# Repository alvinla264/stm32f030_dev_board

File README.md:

# STM32F030 Dev Board

This is a custom development board for the STM32F030RCT6 with USB-C and FT232H for USB-to-serial communication and SWD ports for debugging. Designed as a 4-layer board.

---

## 📷 Schematic

---

## 🖼️ PCB Layout

### 2D Layout:

### 3D Preview:

---

## 🔧 Stackup

- Layer 1 (Top): Signal + GND pours
- Layer 2: GND
- Layer 3: Power (3.3V plane)
- Layer 4 (Bottom): Signal + GND pours

---

## 📌 Features

- STM32F030RCT6 (64-pin LQFP)
- USB-C for power and data
- FT232H for USB-to-UART
- SWD ports for debugging
- Decoupling and filtering capacitors throughout

---

## 💡 Status

- ✔️ Schematic complete
- ✔️ PCB layout complete
- ❌ Via Stitching in progress
- ❌ Testing and fabrication in progress

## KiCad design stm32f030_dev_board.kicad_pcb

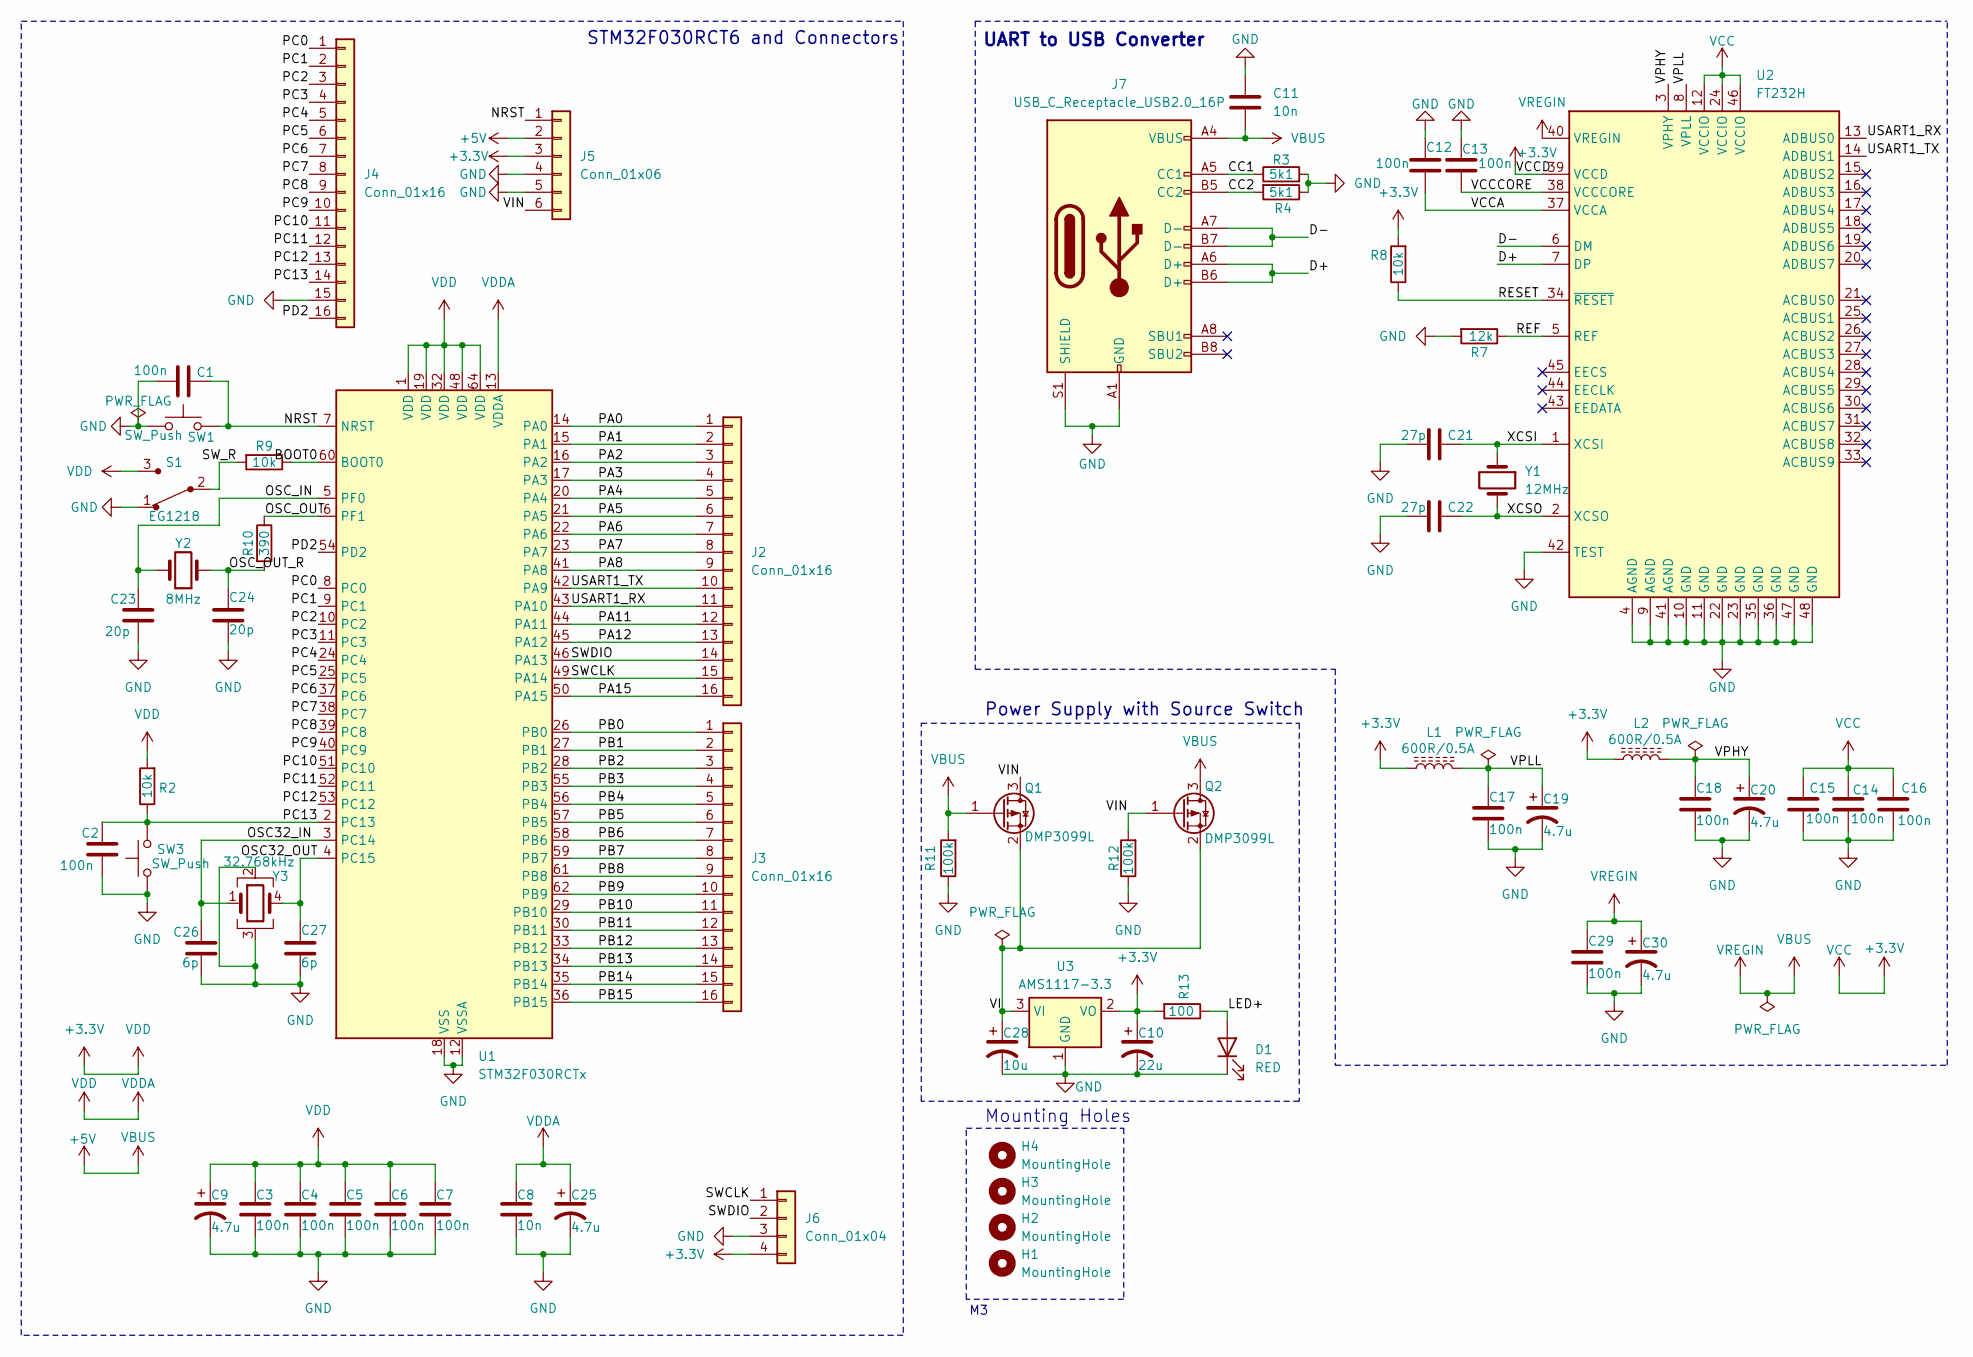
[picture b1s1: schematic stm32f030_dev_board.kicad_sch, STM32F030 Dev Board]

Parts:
C1, C2, C3, C4, C5, C6, C7, C12, C13, C14, C15, C16, C17, C18, C29: 100n; C_0402_1005Metric_Pad0.74x0.62mm_HandSolder
C8, C11: 10n; C_0402_1005Metric_Pad0.74x0.62mm_HandSolder
C9, C19, C20, C25, C30: 4.7u; CP_EIA-3216-18_Kemet-A_Pad1.58x1.35mm_HandSolder
C10: 22u; CP_EIA-3216-18_Kemet-A_Pad1.58x1.35mm_HandSolder
C21, C22: 27p; C_0402_1005Metric_Pad0.74x0.62mm_HandSolder
C23, C24: 20p; C_0603_1608Metric_Pad1.08x0.95mm_HandSolder
C26, C27: 6p; C_0603_1608Metric_Pad1.08x0.95mm_HandSolder
C28: 10u; CP_EIA-6032-28_Kemet-C_Pad2.25x2.35mm_HandSolder
D1: RED; C_0402_1005Metric_Pad0.74x0.62mm_HandSolder
H1, H2, H3, H4: MountingHole; MountingHole_2.2mm_M2
J2, J3, J4: Conn_01x16; PinSocket_1x16_P2.54mm_Vertical
J5: Conn_01x06; PinSocket_1x06_P2.54mm_Vertical
J6: Conn_01x04; PinSocket_1x04_P2.54mm_Vertical
J7: USB_C_Receptacle_USB2.0_16P; USB_C_Receptacle_GCT_USB4105-xx-A_16P_TopMnt_Horizontal
L1, L2: 600R/0.5A; L_1206_3216Metric_Pad1.22x1.90mm_HandSolder
Q1, Q2: DMP3099L; SOT-23
R2, R8, R9: 10k; R_0603_1608Metric_Pad0.98x0.95mm_HandSolder
R3, R4: 5k1; R_0603_1608Metric_Pad0.98x0.95mm_HandSolder
R7: 12k; R_0603_1608Metric_Pad0.98x0.95mm_HandSolder
R10: 390; R_0603_1608Metric_Pad0.98x0.95mm_HandSolder
R11, R12: 100k; R_0603_1608Metric_Pad0.98x0.95mm_HandSolder
R13: 100; R_0603_1608Metric_Pad0.98x0.95mm_HandSolder
S1: EG1218; Switch_Slide_11.6x4mm_EG1218; MPN EG1218; Digi-Key_PN EG1903-ND
SW1, SW3: SW_Push; SW_PUSH_6mm_H5mm
U1: STM32F030RCTx; LQFP-64_10x10mm_P0.5mm
U2: FT232H; LQFP-48_7x7mm_P0.5mm
U3: AMS1117-3.3; SOT-223-3_TabPin2
Y1: 12MHz; Crystal_HC49-4H_Vertical
Y2: 8MHz; Crystal_HC49-4H_Vertical
Y3: 32.768kHz; Crystal_SMD_Abracon_ABS25-4Pin_8.0x3.8mm

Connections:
+3.3V: C3.1, C4.1, C5.1, C6.1, C7.1, C8.1, C9.1, C10.1, C14.1, C15.1, C16.1, C25.1, J5.3, J6.4, L1.1, L2.1, R2.2, R8.2, R13.2, S1.3, U1.1 (VDD), U1.13 (VDDA), U1.19 (VDD), U1.32 (VDD), U1.48 (VDD), U1.64 (VDD), U2.12 (VCCIO), U2.24 (VCCIO), U2.39 (VCCD), U2.46 (VCCIO), U3.2 (VO)
+5V: C11.2, C29.1, C30.1, J5.2, J7.A4 (VBUS), J7.A9 (VBUS), J7.B4 (VBUS), J7.B9 (VBUS), Q1.1 (G), Q2.3 (D), R11.2, U2.40 (VREGIN)
/BOOT0: R9.1, U1.60 (BOOT0)
/CC1: J7.A5 (CC1), R3.1
/CC2: J7.B5 (CC2), R4.2
/D+: J7.A6 (D+), J7.B6 (D+), U2.7 (DP)
/D-: J7.A7 (D-), J7.B7 (D-), U2.6 (DM)
/LED+: D1.2 (A), R13.1
/NRST: C1.1, J5.1, SW1.2, U1.7 (NRST)
/OSC32_IN: C26.1, U1.3 (PC14), Y3.1
/OSC32_OUT: C27.1, U1.4 (PC15), Y3.4
/OSC_IN: C23.1, U1.5 (PF0), Y2.2
/OSC_OUT: R10.1, U1.6 (PF1)
/OSC_OUT_R: C24.1, R10.2, Y2.1
/PA0: J2.1, U1.14 (PA0)
/PA1: J2.2, U1.15 (PA1)
/PA2: J2.3, U1.16 (PA2)
/PA3: J2.4, U1.17 (PA3)
/PA4: J2.5, U1.20 (PA4)
/PA5: J2.6, U1.21 (PA5)
/PA6: J2.7, U1.22 (PA6)
/PA7: J2.8, U1.23 (PA7)
/PA8: J2.9, U1.41 (PA8)
/PA11: J2.12, U1.44 (PA11)
/PA12: J2.13, U1.45 (PA12)
/PA15: J2.16, U1.50 (PA15)
/PB0: J3.1, U1.26 (PB0)
/PB1: J3.2, U1.27 (PB1)
/PB2: J3.3, U1.28 (PB2)
/PB3: J3.4, U1.55 (PB3)
/PB4: J3.5, U1.56 (PB4)
/PB5: J3.6, U1.57 (PB5)
/PB6: J3.7, U1.58 (PB6)
/PB7: J3.8, U1.59 (PB7)
/PB8: J3.9, U1.61 (PB8)
/PB9: J3.10, U1.62 (PB9)
/PB10: J3.11, U1.29 (PB10)
/PB11: J3.12, U1.30 (PB11)
/PB12: J3.13, U1.33 (PB12)
/PB13: J3.14, U1.34 (PB13)
/PB14: J3.15, U1.35 (PB14)
/PB15: J3.16, U1.36 (PB15)
/PC0: J4.1, U1.8 (PC0)
/PC1: J4.2, U1.9 (PC1)
/PC2: J4.3, U1.10 (PC2)
/PC3: J4.4, U1.11 (PC3)
/PC4: J4.5, U1.24 (PC4)
/PC5: J4.6, U1.25 (PC5)
/PC6: J4.7, U1.37 (PC6)
/PC7: J4.8, U1.38 (PC7)
/PC8: J4.9, U1.39 (PC8)
/PC9: J4.10, U1.40 (PC9)
/PC10: J4.11, U1.51 (PC10)
/PC11: J4.12, U1.52 (PC11)
/PC12: J4.13, U1.53 (PC12)
/PC13: C2.1, J4.14, R2.1, SW3.2, U1.2 (PC13)
/PD2: J4.16, U1.54 (PD2)
/REF: R7.1, U2.5 (REF)
/RESET: R8.1, U2.34 (~RESET)
/SWCLK: J2.15, J6.1, U1.49 (PA14)
/SWDIO: J2.14, J6.2, U1.46 (PA13)
/SW_R: R9.2, S1.2
/USART1_RX: J2.11, U1.43 (PA10), U2.13 (ADBUS0)
/USART1_TX: J2.10, U1.42 (PA9), U2.14 (ADBUS1)
/VCCA: C12.2, U2.37 (VCCA)
/VCCCORE: C13.2, U2.38 (VCCCORE)
/VI: C28.1, Q1.2 (S), Q2.2 (S), U3.3 (VI)
/VIN: J5.6, Q1.3 (D), Q2.1 (G), R12.2
/VPHY: C18.1, C20.1, L2.2, U2.3 (VPHY)
/VPLL: C17.1, C19.1, L1.2, U2.8 (VPLL)
/XCSI: C21.1, U2.1 (XCSI), Y1.1
/XCSO: C22.1, U2.2 (XCSO), Y1.2
GND: C1.2, C2.2, C3.2, C4.2, C5.2, C6.2, C7.2, C8.2, C9.2, C10.2, C11.1, C12.1, C13.1, C14.2, C15.2, C16.2, C17.2, C18.2, C19.2, C20.2, C21.2, C22.2, C23.2, C24.2, C25.2, C26.2, C27.2, C28.2, C29.2, C30.2, D1.1 (K), J4.15, J5.4, J5.5, J6.3, J7.A1 (GND), J7.A1-B12 (GND), J7.A12 (GND), J7.B1 (GND), J7.B1-A12 (GND), J7.B12 (GND), J7.S1 (SHIELD), R3.2, R4.1, R7.2, R11.1, R12.1, S1.1, SW1.1, SW3.1, U1.12 (VSSA), U1.18 (VSS), U1.31 (VSS), U1.47 (VSS), U1.63 (VSS), U2.4 (AGND), U2.9 (AGND), U2.10 (GND), U2.11 (GND), U2.22 (GND), U2.23 (GND), U2.35 (GND), U2.36 (GND), U2.41 (AGND), U2.42 (TEST), U2.47 (GND), U2.48 (GND), U3.1 (GND), Y3.2, Y3.3

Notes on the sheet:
Mounting Holes
UART to USB Converter
STM32F030RCT6 and Connectors
Power Supply with Source Switch

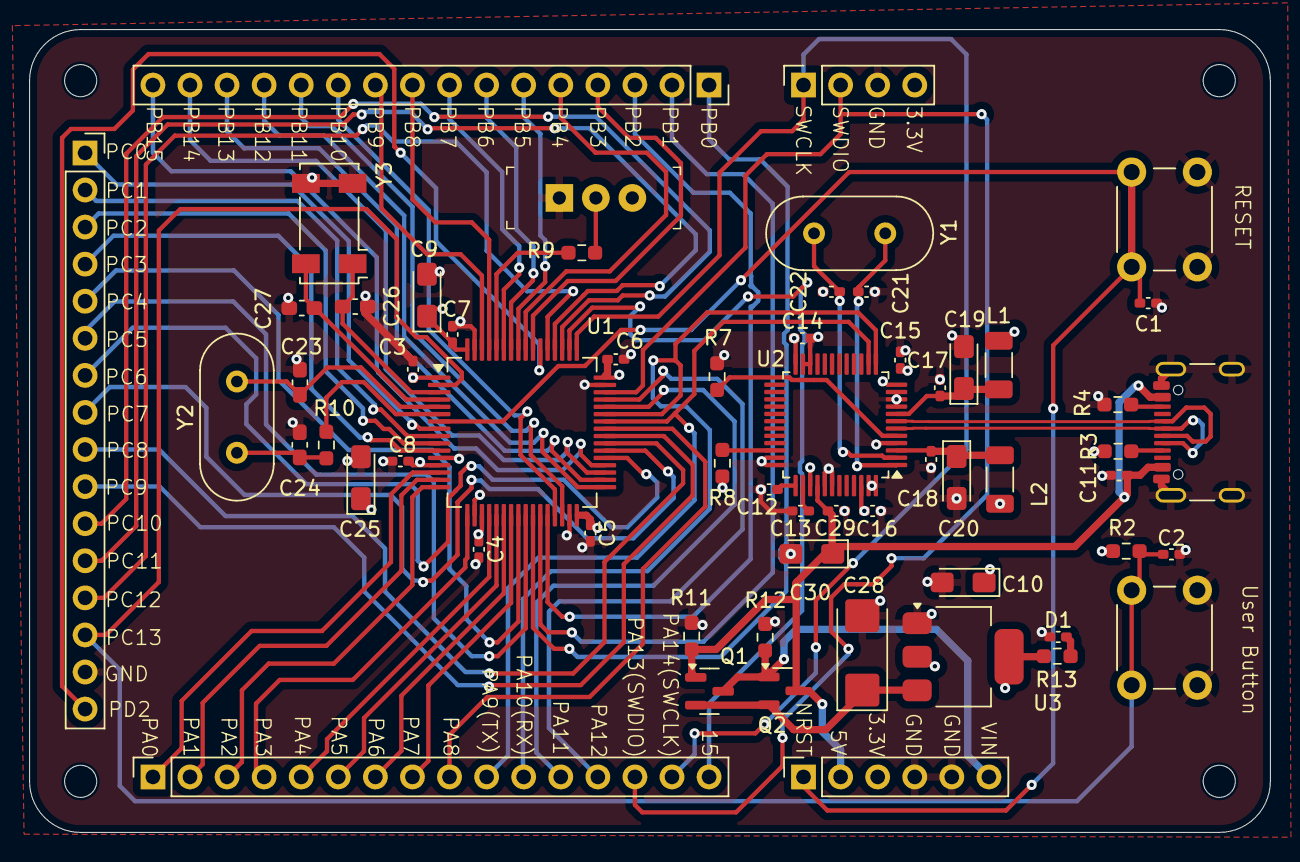
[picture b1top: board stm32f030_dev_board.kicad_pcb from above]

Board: 4 copper layers, 85.0 x 55.0 mm, 64 parts (0 on the bottom side), 73 nets.

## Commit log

2025-05-02 Started PCB layout and added net labels to schematic
2025-05-03 Layout the pcb and added mounting holes to schematic and pcb
2025-05-03 Fix Edge Cuts to have rounded corners
2025-05-03 Adjusted Spacing between pin headers
2025-05-05 removed D+ and D- resistors, finished routing front and back copper, moved button to better place
2025-05-06 Finished routing, Added silk screen labels for ports, fixed USB C footprint(removed stacked pads for ground pins)
2025-05-07 added .gitignore
2025-05-07 fixed silkscreen overlap and updated .gitignore
2025-05-10 Switched to 4 layer board stackup and rerouted
2025-05-10 Added readme
2025-05-10 Added images folder for readme
2025-05-10 Fixed 2d pcb image and readme
